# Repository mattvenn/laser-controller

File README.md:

# Epilog 32 ex usage & control system

## Control System

* internet connection to download current valid RFID cards
* enable laser with valid RFID card
* post usage to net every minute
* disable laser after X seconds without laser being used

### Electronics

* ESP8266
* 2 channel relay & driver
* RFID reader
* ws2812 RGB status light

* [photo of pcb](https://goo.gl/photos/raj6Eu2eDnTMet147)
* [pdf schematic](control-board/schematic.pdf)

#### Problems & Fixes

* Sometimes rfid reader seems to get blocked
* Sometimes laser pulse isn't detected so laser is switched off - fixed by
 Guillem, was an interrupt issue
* Sometimes relay turns on but laser won't fire - fixed with new pcb (breadboard
 bad ground connections)
 
### Software

* ESP8266 checks RFID against remote DB
* if valid, light LED
* turn on relay to connect DSUB25 lines 7&8.
* laser DSUB25 pin 7 -> interrupt on pin 14,
* while interrupt is firing post usage to phant

[esp8266 firmware](firmware/src/)

[Dashboard](http://freeboard.cursivedata.co.uk/index.html?load=dust.json)

[Logs](http://phant.cursivedata.co.uk/streams/kBd098lqXzu3mYJOX9YYckorrEy)

## Control reverse engineering

Neither Epilog or Coherent were willing to share the DSUB 25 pinout that controls the Coherent C Series laser model 1138402-AA.

Searching for the DSUB 25 format, only references to [ILDA](https://www.laserworld.com/en/show-laser-light-faq/technical-show-laser-faq/laser-projectors-technical-faq/1140-how-is-the-ilda-connector-pinout.html) were found.

A [board](bob/) that connects straight through 2 x DSUB 25 was designed in Kicad and milled

After finding system ground, all pins were tested with laser on and off:

| Pin | Laser On | Laser Off | 
| --- | -------- | --------- |
|1|0|0
|2|0|0
|3|5|5
|4|0|0
|5|0|0
|6|5|5
|7|5->0|0
|8|5|5
|9|5|5
|10|5|5
|11|5|5
|12|5|5
|13|0|0
|14|5|5
|15|5|5
|16|GND|GND
|17|0|0
|18|0|0
|19|0|0
|20|0->5|5
|21|0|0
|22|5|5
|23|5|5
|24|5|5
|25|15|15

Only pins 7 & 20 seemed to have any change when lasing. Also thought that they would be a differential signal.
Cracking out the scope gave these results for rastering, lasing at 50% power and 100% power.

Scope channel 1 is pin 7, channel 2 is 20.

Breaking connection to either pin 7 or 20 made no difference, only breaking both lines stopped the laser.

Also tested was breaking pin 4 as ILDA showed that as being the interlock signal, it made no difference.

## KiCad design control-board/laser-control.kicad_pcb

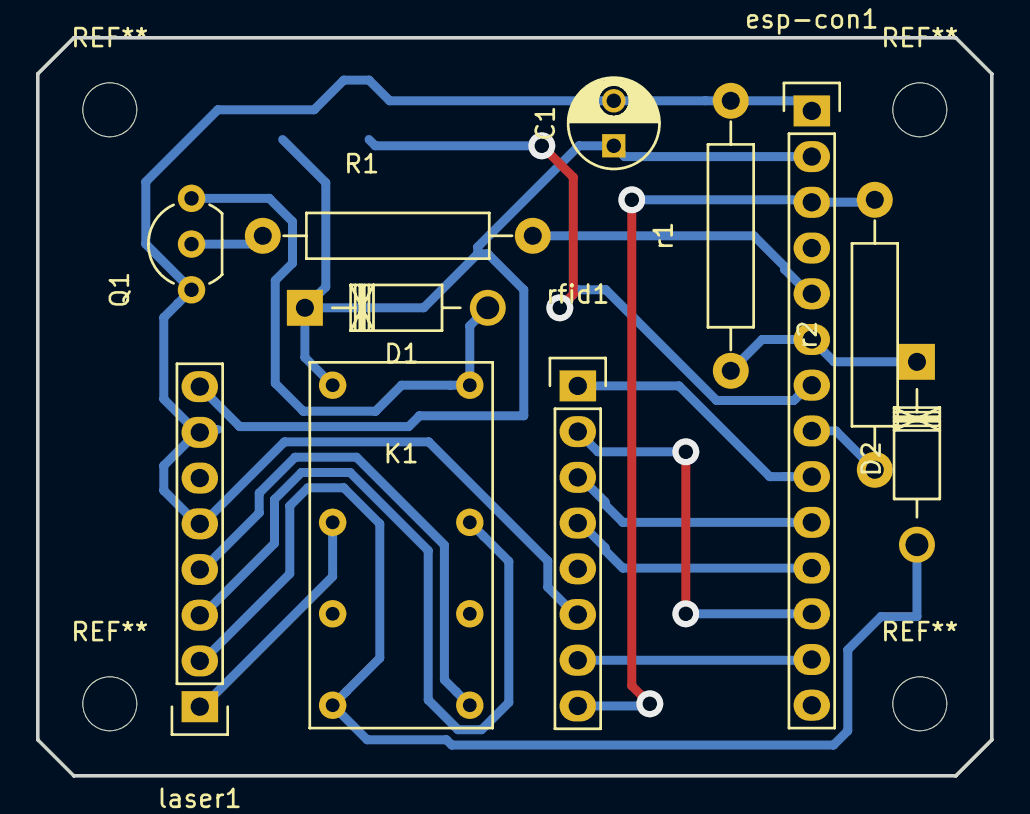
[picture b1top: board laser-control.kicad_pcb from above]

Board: 2 copper layers, 53.0 x 41.0 mm, 12 parts (1 on the bottom side), 18 nets.

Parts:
C1: CP; C_Radial_D5_L6_P2.5
D1, D2: D; Diode_DO-41_SOD81_Horizontal_RM10
K1: RELAY_2RT; relay
Q1: Q_NPN_EBC; TO-92_Inline_Wide
R1: 330r; Resistor_Horizontal_RM15mm
esp-con1: CONN_01X14; Pin_Header_Straight_1x14
laser1: CONN_01X08; Pin_Header_Straight_1x08
led1: ws2812b; WS2812B
r1, r2: 10k; Resistor_Horizontal_RM15mm
rfid1: CONN_01X08; Pin_Header_Straight_1x08

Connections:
+3V3: esp-con1.3, r2.2, rfid1.8
+5V: C1.1, D1.1, K1.8, esp-con1.2, laser1.8, led1.1
/a-in: K1.12, laser1.1
/a-out: D2.2, K1.16, laser1.2
/b-in: K1.5, laser1.3
/b-out: K1.1, laser1.4
/laser-on: R1.2, esp-con1.5
/laser-sense: D2.1, esp-con1.6, r1.1
/miso: esp-con1.11, rfid1.4
/mosi: esp-con1.10, rfid1.3
/rst: esp-con1.13, rfid1.7
/sck: esp-con1.12, rfid1.2
/ss: esp-con1.9, rfid1.1
/ws2812: esp-con1.7, led1.4
GND: C1.2, Q1.1, esp-con1.1, laser1.5, laser1.7, led1.3, r1.2, rfid1.6
unnamed: D1.2, K1.9, Q1.3
unnamed: Q1.2, R1.1
unnamed: esp-con1.8, r2.1

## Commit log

2017-01-12 docs
2017-01-12 net & schematic
2017-01-13 firmware first draft
2017-01-13 phant notes
2017-01-13 rfid working demo
2017-01-13 after validating rfid, dont turn off laser if net is down
2017-01-13 sw overview
2017-01-16 only allow one rfid
2017-01-25 add users and increases laser time delay
2017-01-26 Calculate costs
2017-01-30 External diode protection
2017-02-02 total and warn if missing user
2017-02-02 split into 2 state machines
2017-02-02 disable interrupts while waiting for rfid
2017-02-02 comment
2017-02-03 move laser detection to auth state machine, tidy up and increased timeouts
2017-02-16 changed for constalog
2017-02-16 feetch remote list of valid users
2017-02-16 get users from csv
2017-02-16 notes on electronic changes
2017-02-20 debugging
2017-02-22 disable interrupts while checking time
2017-03-09 ws2812 added
2017-03-09 higher serial speed
2017-03-09 laser control board
2017-03-09 pdf schematic
2017-03-09 notes on pcb
2017-04-03 added Luis
2017-04-03 fetch csv
2017-04-03 deal with missing records
2017-05-19 month and logging
2018-01-10 fix up broken date stuff
2021-03-17 fix isr issue
2021-03-17 template
